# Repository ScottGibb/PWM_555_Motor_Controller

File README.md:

# PWM_555_Motor_Controller
A Simple PCB that contains a 555 timer for PWM control of various small motors. The design approach taken was to use leftover components from different salvages over the years to see what could be built that might be of use. This ended up being a PWM Controller using a 555 Timer. The CAD model of the PCB is shown below:

# Design
As previously mentioned, the purpose of this PCB was to use existing parts and try something new that wasn't microcontroller based. This is why the 555 Timer was used along with a BJT transistor. The populated PCB can be seen below along with the Veroboard version:

# Improvements
As for design improvements, a lot of improvements can be made:

- Swap to fully SMT design as this will reduce EMI and create a better layout.
- Swap BJT for FET as this will reduce current consumption and stop the transistor from heating up during the PWM cycle.
- Due to the low current nature of the design, swapping screw terminals for JSTs would be appropriate as this would yield a better-looking design. It will also reduce the overkill of using 15A-rated terminals for a PCB used to control small motors.

# Software Requirements
The following software packages are required for this project:
- [Eagle](https://www.autodesk.co.uk/products/eagle/overview?term=1-YEAR&tab=subscription)
- [Fusion 360](https://www.autodesk.com/products/fusion-360/overview?term=1-YEAR&tab=subscription)

# Useful Links
- [Thingiverse Case](https://www.thingiverse.com/thing:4596800)
- [JLCPCB](https://jlcpcb.com/)
- [555 Timers](https://electronicsclub.info/555timer.htm)
- [Adjustable PWM 555 Timer](https://www.electronicshub.org/555-timer-pwm/)

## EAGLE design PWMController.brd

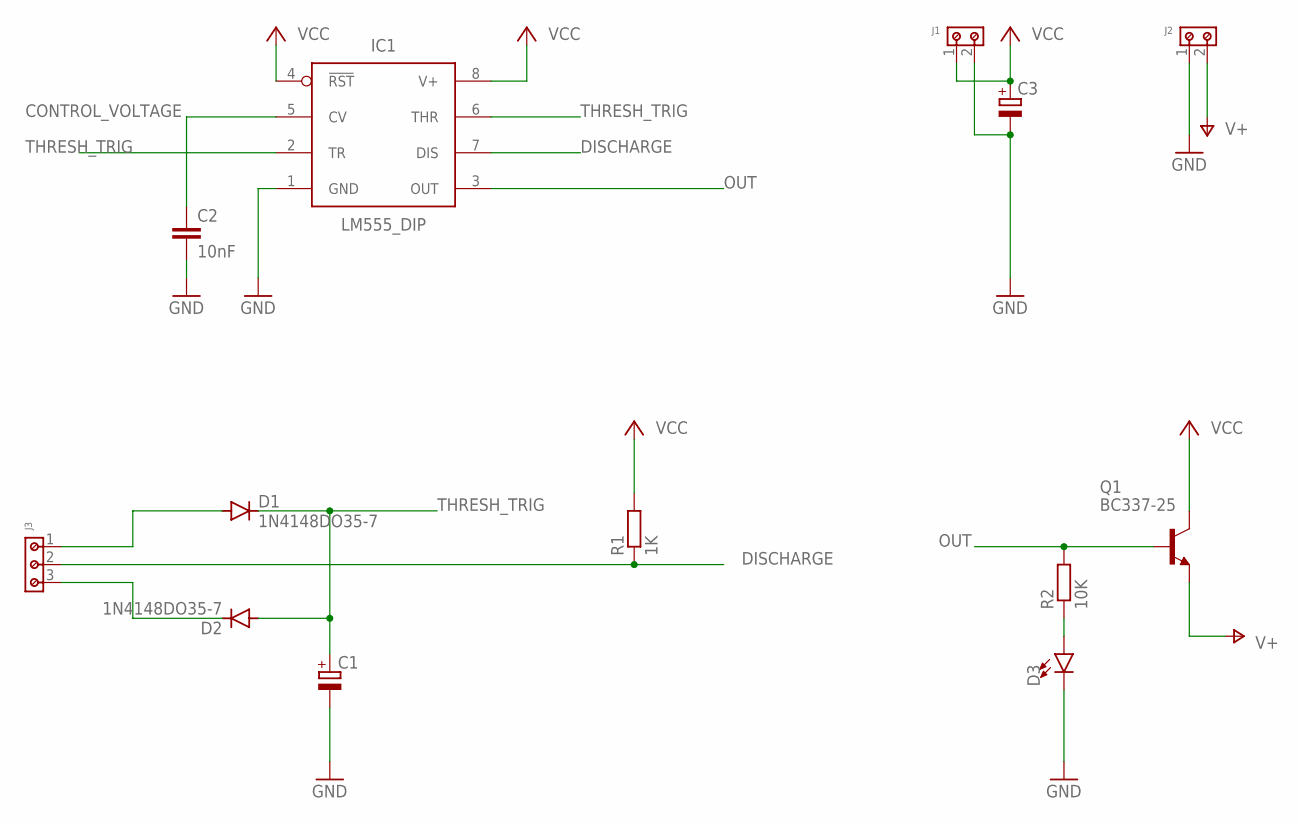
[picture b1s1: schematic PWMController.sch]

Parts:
C1: 2.2uF; E1,8-4
C2: 10nF; CAPC3216X135
C3: 100mF; E1,8-4
D1, D2: 1N4148DO35-7; DO35-7
D3: LED5MM
IC1: LM555_DIP; DIP826W53P254L959H508Q8B
J1, J2: 691213510002
J3: 691213510003
Q1: BC337-25; TO92
R1: 1K; R1206
R2: 10K; R1206

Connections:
CONTROL_VOLTAGE: C2.1, IC1.5 (CV)
DISCHARGE: IC1.7 (DIS), J3.2, R1.1
GND: C1.-, C2.2, C3.-, D3.K (C), IC1.1 (GND), J1.2, J2.1
unnamed: D1.A, J3.1
unnamed: D3.A, R2.1
unnamed: D2.C, J3.3
OUT: IC1.3 (OUT), Q1.2 (B), R2.2
THRESH_TRIG: C1.+, D1.C, D2.A, IC1.2 (TR), IC1.6 (THR)
V+: J2.2, Q1.1 (E)
VCC: C3.+, IC1.4 (!RST), IC1.8 (V+), J1.1, Q1.3 (C), R1.2

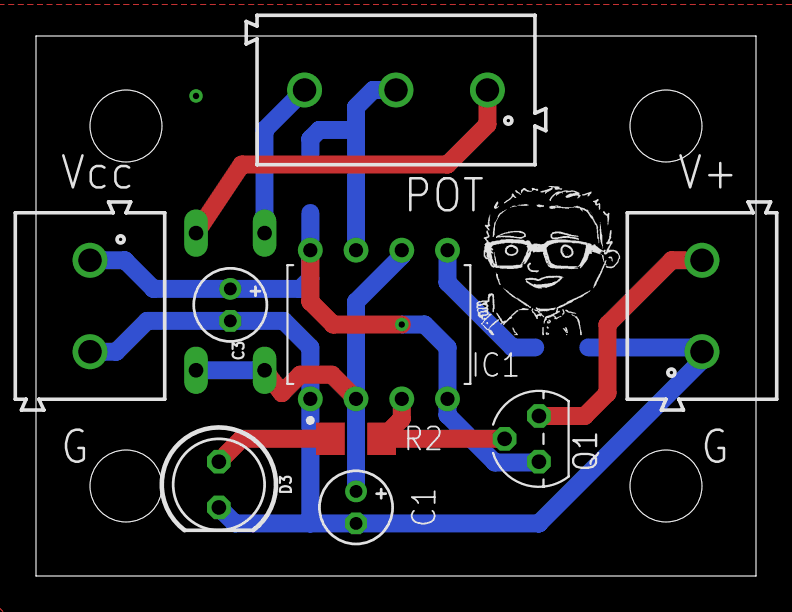
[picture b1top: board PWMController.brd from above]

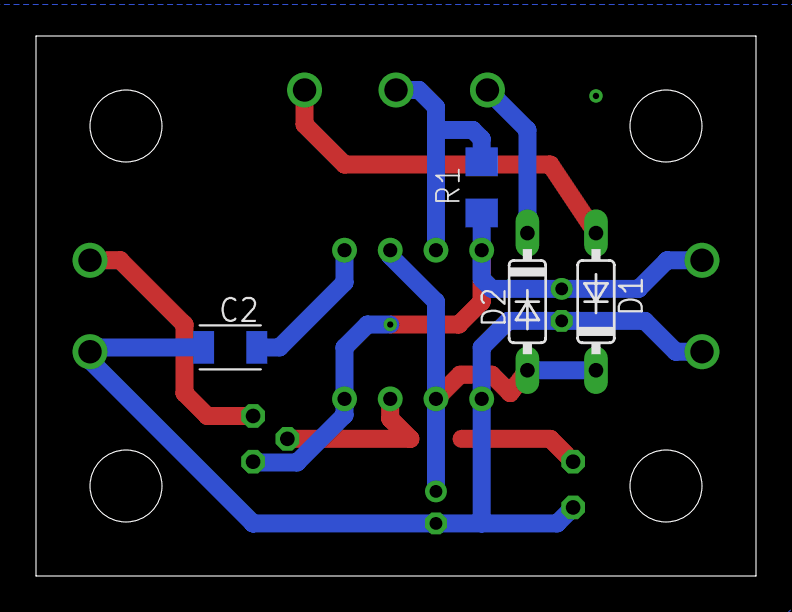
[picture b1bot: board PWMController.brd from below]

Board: 2 copper layers, 40.0 x 30.0 mm, 13 parts (4 on the bottom side), 10 nets.

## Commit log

2020-09-14 Adding Initial Commit
2020-09-14 Changing ReadMe Files
2020-09-27 Adding updated files
2022-03-13 Create LICENSE
2022-09-28 Adding updated .gitignore
2022-09-28 Adding 3D Model png as well as updated ReadMe
2022-09-28 Adding updated ReadMe
2022-09-28 Adding links to ReadMe
2022-09-28 Added Spelling and Grammar Check
2022-09-28 Adding Logo and updating PCB Silkscreen
2022-09-28 Adding JLCPCB Order Submission
2022-10-15 Adding Schematic components update and populated PCB pictures

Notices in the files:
parts and their libraries:
Wurth_Connectors_WR-TBL Rising Cage Clam: Copyright: Würth Elektronik
